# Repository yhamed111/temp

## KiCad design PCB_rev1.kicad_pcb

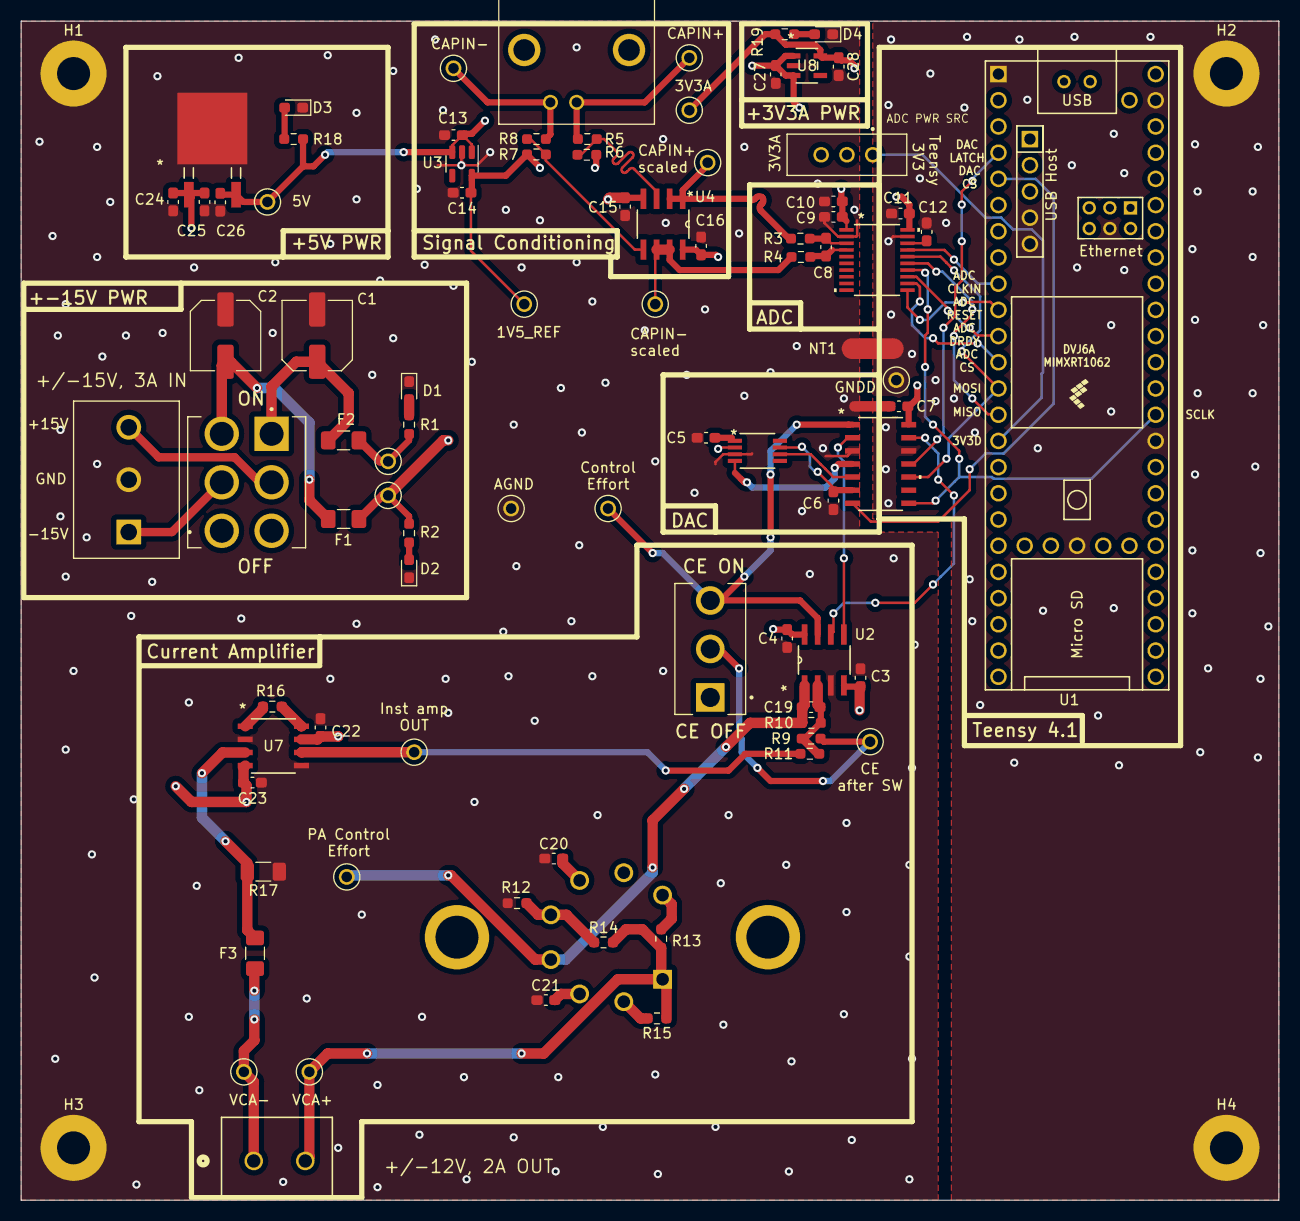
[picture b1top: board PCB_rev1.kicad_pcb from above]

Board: 4 copper layers, 121.9 x 114.3 mm, 91 parts (1 on the bottom side), 54 nets.

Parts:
4.096V_REF1: MAX6126B41+; 21-0036K
15V/5V_linear_regulator1: NCP5501DT50RKG; DPAK-3_ONS
+/-15V_PWR1: 3_term_conn; CUI_TB007-508-03BE
ADC1: ADS131M02IPWR; TSSOP20_PW_TEX
C1, C2: 220uF; C_Elec_6.3x7.7
C3, C4, C5, C6, C7, C9, C15, C16, C25: 100nF; C_0603_1608Metric_Pad1.08x0.95mm_HandSolder
C8: 10nF; C_0603_1608Metric_Pad1.08x0.95mm_HandSolder
C10, C11, C13, C14, C20, C21, C22, C23, C27, C28: 1uF; C_0603_1608Metric_Pad1.08x0.95mm_HandSolder
C12: 220nF; C_0603_1608Metric_Pad1.08x0.95mm_HandSolder
C19: 10pF; C_0603_1608Metric_Pad1.08x0.95mm_HandSolder
C24: 10uF; C_0603_1608Metric_Pad1.08x0.95mm_HandSolder
C26: 4.7uF; C_0603_1608Metric_Pad1.08x0.95mm_HandSolder
Cap_probe_output1: Conn_Coaxial; TE_5227161-2
D1, D2, D3, D4: LED; D_0603_1608Metric_Pad1.05x0.95mm_HandSolder
DAC1: MAX5719AGSD+; 21-0041_S14&plus_4_MXM
F1, F2, F3: Fuse; Fuse_1206_3216Metric_Pad1.42x1.75mm_HandSolder
H1, H2, H3, H4: MountingHole_Pad; MountingHole_3.2mm_M3_Pad
J1: 2_term_conn; CONN_TB002-500-02BE_CUD
NT1: NetTie_2; NetTie-2_SMD_Pad2.0mm
R1, R2: 22K; R_0603_1608Metric_Pad0.98x0.95mm_HandSolder
R3, R4, R10: 1K; R_0603_1608Metric_Pad0.98x0.95mm_HandSolder
R5, R8: 100K; R_0603_1608Metric_Pad0.98x0.95mm_HandSolder
R6, R7: 15K; R_0603_1608Metric_Pad0.98x0.95mm_HandSolder
R9: 750R; R_0603_1608Metric_Pad0.98x0.95mm_HandSolder
R11: 4.5K; R_0603_1608Metric_Pad0.98x0.95mm_HandSolder
R12: 10K; R_0603_1608Metric_Pad0.98x0.95mm_HandSolder
R13, R15: 0.1R; R_0603_1608Metric_Pad0.98x0.95mm_HandSolder
R14: 50K; R_0603_1608Metric_Pad0.98x0.95mm_HandSolder
R16: 470R; R_0603_1608Metric_Pad0.98x0.95mm_HandSolder
R17: 0.05R; R_1206_3216Metric_Pad1.30x1.75mm_HandSolder
R18, R19: 4.7K; R_0603_1608Metric_Pad0.98x0.95mm_HandSolder
S1: 3V3A/3V3D; SW_EG1218
SW1: SW_SPDT; SW_100SP1T1B4M2QE
SW2: PWR_SW; SW_100DP1T1B1M1QEH
TP1: CAP_P; KEYSTONE_5117
TP2: CAP_N; KEYSTONE_5117
TP3: AGND; KEYSTONE_5117
TP4: +15V; KEYSTONE_5117
TP5: -15V; KEYSTONE_5117
TP6: CAP_scaled_P; KEYSTONE_5117
TP7: CAP_scaled_N; KEYSTONE_5117
TP8: DGND; KEYSTONE_5117
TP9: control_effort; KEYSTONE_5117
TP10: 1V5_REF; KEYSTONE_5117
TP11: PA_IN+; KEYSTONE_5117
TP12: Inst_amp_OUT; KEYSTONE_5117
TP13: VCA+; KEYSTONE_5117
TP14: VCA-; KEYSTONE_5117
TP15: 5V; KEYSTONE_5117
TP16: 3V; KEYSTONE_5117
TP17: control_effort_after_SW; KEYSTONE_5117
U1: Teensy4.1; Teensy41
U2, U4: LM358; D8
U3: TLV70215_SOT23-5; SOT-23-5
U6: PA12; PA08
U7: instrumentation_amp1; SO-8_S_LIT
U8: MIC5504-3.3YM5-TR; SOT-23-5_MC_MCH

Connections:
+3.3VA: ADC1.1 (AVDD), C9.2, C10.2, C28.1, R19.1, S1.3, TP16.TP, U8.5 (VOUT)
+3V3: S1.1, U1.15 (3V3)
+5V: 4.096V_REF1.2 (IN), 15V/5V_linear_regulator1.3 (VOUT), C7.1, C13.2, C26.1, C27.2, DAC1.14 (VDD), R18.1, TP15.TP, U3.1 (IN), U3.3 (EN), U8.1 (VIN), U8.3 (EN)
+15V: 15V/5V_linear_regulator1.1 (VIN), C4.1, C16.1, C21.2, C22.1, C24.1, C25.1, F2.2, R1.1, TP4.TP, U2.8 (V+), U4.8 (V+), U6.3 (+VS), U7.7 (+VS)
-15V: C3.1, C15.1, C20.2, C23.2, F1.1, R2.1, TP5.TP, U2.4 (V-), U4.4 (V-), U6.6 (-VS), U7.4 (-VS)
/+15V_PWR: +/-15V_PWR1.3, SW2.2 (B)
/-15V_PWR: +/-15V_PWR1.1, SW2.5 (B)
/ADC_CLKIN: ADC1.17 (CLKIN), U1.9 (7_RX2_OUT1A)
/ADC_DRDY: ADC1.13 (*DRDY), U1.11 (9_OUT1C)
/ADC_RESET: ADC1.11 (*SYNC/*RESET), U1.10 (8_TX2_IN1)
/AIN0N: R4.1, TP7.TP, U4.6 (-), U4.7
/AIN0P: R3.1, TP6.TP, U4.1, U4.2 (-)
/CAP_IN_N: Cap_probe_output1.2 (Ext), R8.1, TP2.TP
/CAP_IN_P: Cap_probe_output1.1 (In), R5.1, TP1.TP
/Control_Effort: DAC1.1 (RFB), SW1.3 (C), TP9.TP, U2.7
/Current_Amplifier/PA_control_effort: C19.1, R10.2, TP11.TP, U2.1, U6.4 (+IN)
/Current_Amplifier/VIN: R9.1, SW1.2 (B), TP17.TP
/Current_Amplifier/inst_amp_out: R11.2, TP12.TP, U7.6 (OUTPUT)
/DAC/AAGNDS: 4.096V_REF1.4 (GNDS), DAC1.4 (AGNDS)
/DAC/DAC_INV: DAC1.13 (INV), U2.6 (-)
/DAC/FORCE_REF: 4.096V_REF1.7 (OUTF), C6.1, DAC1.6 (REFF)
/DAC/NR: 4.096V_REF1.1 (NR), C5.1
/DAC/RAW_OUT: DAC1.2 (OUT), U2.5 (+)
/DAC/SENSE_REF: 4.096V_REF1.6 (OUTS), DAC1.5 (REFS)
/DAC_LATCH: DAC1.11 (*LDAC), U1.4 (2_OUT2)
/SPI_ADC_CS: ADC1.12 (*CS), U1.12 (10_CS_MQSR)
/SPI_DAC_CS: DAC1.7 (*CS), U1.5 (3_LRCLK2)
/SPI_MISO: ADC1.15 (DOUT), U1.14 (12_MISO_MQSL)
/SPI_MOSI: ADC1.16 (DIN), DAC1.10 (DIN), U1.13 (11_MOSI_CTX1)
/SPI_SCLK: ADC1.14 (SCLK), DAC1.8 (SCLK), U1.35 (13_SCK_LED)
/Signal_scaling/1V5_REF: C14.2, R6.2, R7.2, TP10.TP, U3.5 (OUT)
/Signal_scaling/OpAmp_IN_N: R7.1, R8.2, U4.5 (+)
/Signal_scaling/OpAmp_IN_P: R5.2, R6.1, U4.3 (+)
/VCA+: J1.2, R13.1, R14.2, R15.1, TP13.TP, U6.1 (OUT)
/VCA-: F3.1, J1.1, TP14.TP
GND: 4.096V_REF1.3 (GND), 15V/5V_linear_regulator1.2 (GND), +/-15V_PWR1.2, ADC1.2 (AGND), C1.2, C2.1, C3.2, C4.2, C5.2, C6.2, C7.2, C9.1, C10.1, C13.1, C14.1, C15.2, C16.2, C20.1, C21.1, C22.2, C23.1, C24.2, C25.2, C26.2, C27.1, C28.2, D1.1 (K), D2.1 (K), D3.1 (K), D4.1 (K), DAC1.3 (AGNDF), H1.1, H3.1, NT1.1, R12.2, R17.1, TP3.TP, U2.3 (+), U3.2 (GND), U7.2 (-IN), U7.5 (REF), U8.2 (GND)
GNDD: ADC1.19 (DGND), C11.2, C12.1, DAC1.12 (DGND), H2.1, H4.1, NT1.2, TP8.TP, U1.1 (GND), U1.34 (GND), U1.47 (GND), U1.52 (GND), U1.58 (GND), U1.59 (GND), U1.64 (GND)
unnamed: ADC1.4 (AIN0N), C8.2, R4.2
unnamed: ADC1.3 (AIN0P), C8.1, R3.2
unnamed: ADC1.18 (CAP), C12.2
unnamed: ADC1.20 (DVDD), C11.1, S1.2
unnamed: D1.2 (A), R1.2
unnamed: D2.2 (A), R2.2
unnamed: D3.2 (A), R18.2
unnamed: D4.2 (A), R19.2
unnamed: R16.1, U7.8 (RG)
unnamed: R16.2, U7.1 (RG)
unnamed: C1.1, F2.1, SW2.1 (A)
unnamed: C2.2, F1.2, SW2.4 (A)
unnamed: C19.2, R9.2, R10.1, R11.1, U2.2 (-)
unnamed: R12.1, R14.1, U6.5 (-IN)
unnamed: R15.2, U6.2 (CL+)
unnamed: R13.2, U6.8 (CL-)
unnamed: F3.2, R17.2, U7.3 (+IN)
